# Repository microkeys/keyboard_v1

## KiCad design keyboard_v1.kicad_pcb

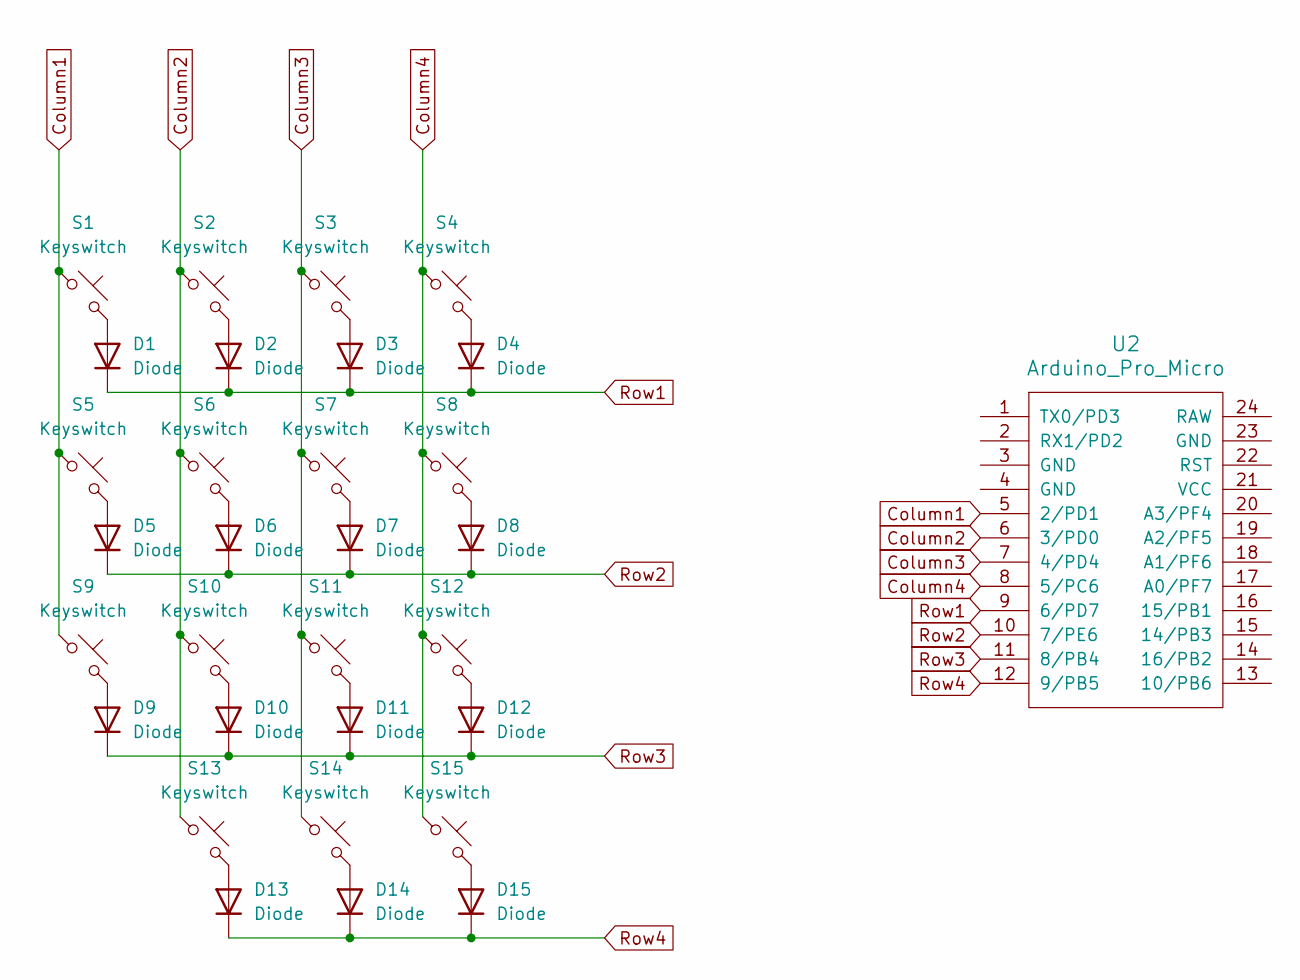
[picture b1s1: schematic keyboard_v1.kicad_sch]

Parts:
D1, D2, D3, D4, D5, D6, D7, D8, D9, D10, D11, D12, D13, D14, D15: Diode; Diode_SOD-123
S1, S2, S3, S4, S5, S6, S7, S8, S9, S10, S11, S12, S13, S14, S15: Keyswitch; MX_PCB_1.00u
U2: Arduino_Pro_Micro

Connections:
Column1: S1.1, S5.1, S9.1, U2.5 (2/PD1)
Column2: S2.1, S6.1, S10.1, S13.1, U2.6 (3/PD0)
Column3: S3.1, S7.1, S11.1, S14.1, U2.7 (4/PD4)
Column4: S4.1, S8.1, S12.1, S15.1, U2.8 (5/PC6)
unnamed: D1.2 (A), S1.2
unnamed: D2.2 (A), S2.2
unnamed: D3.2 (A), S3.2
unnamed: D4.2 (A), S4.2
unnamed: D5.2 (A), S5.2
unnamed: D6.2 (A), S6.2
unnamed: D7.2 (A), S7.2
unnamed: D8.2 (A), S8.2
unnamed: D9.2 (A), S9.2
unnamed: D10.2 (A), S10.2
unnamed: D11.2 (A), S11.2
unnamed: D12.2 (A), S12.2
unnamed: D13.2 (A), S13.2
unnamed: D14.2 (A), S14.2
unnamed: D15.2 (A), S15.2
Row1: D1.1 (K), D2.1 (K), D3.1 (K), D4.1 (K), U2.9 (6/PD7)
Row2: D5.1 (K), D6.1 (K), D7.1 (K), D8.1 (K), U2.10 (7/PE6)
Row3: D9.1 (K), D10.1 (K), D11.1 (K), D12.1 (K), U2.11 (8/PB4)
Row4: D13.1 (K), D14.1 (K), D15.1 (K), U2.12 (9/PB5)

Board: 2 copper layers, 31 parts (15 on the bottom side), 23 nets, no tracks yet.

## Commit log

2023-12-09 Working keyboard?
